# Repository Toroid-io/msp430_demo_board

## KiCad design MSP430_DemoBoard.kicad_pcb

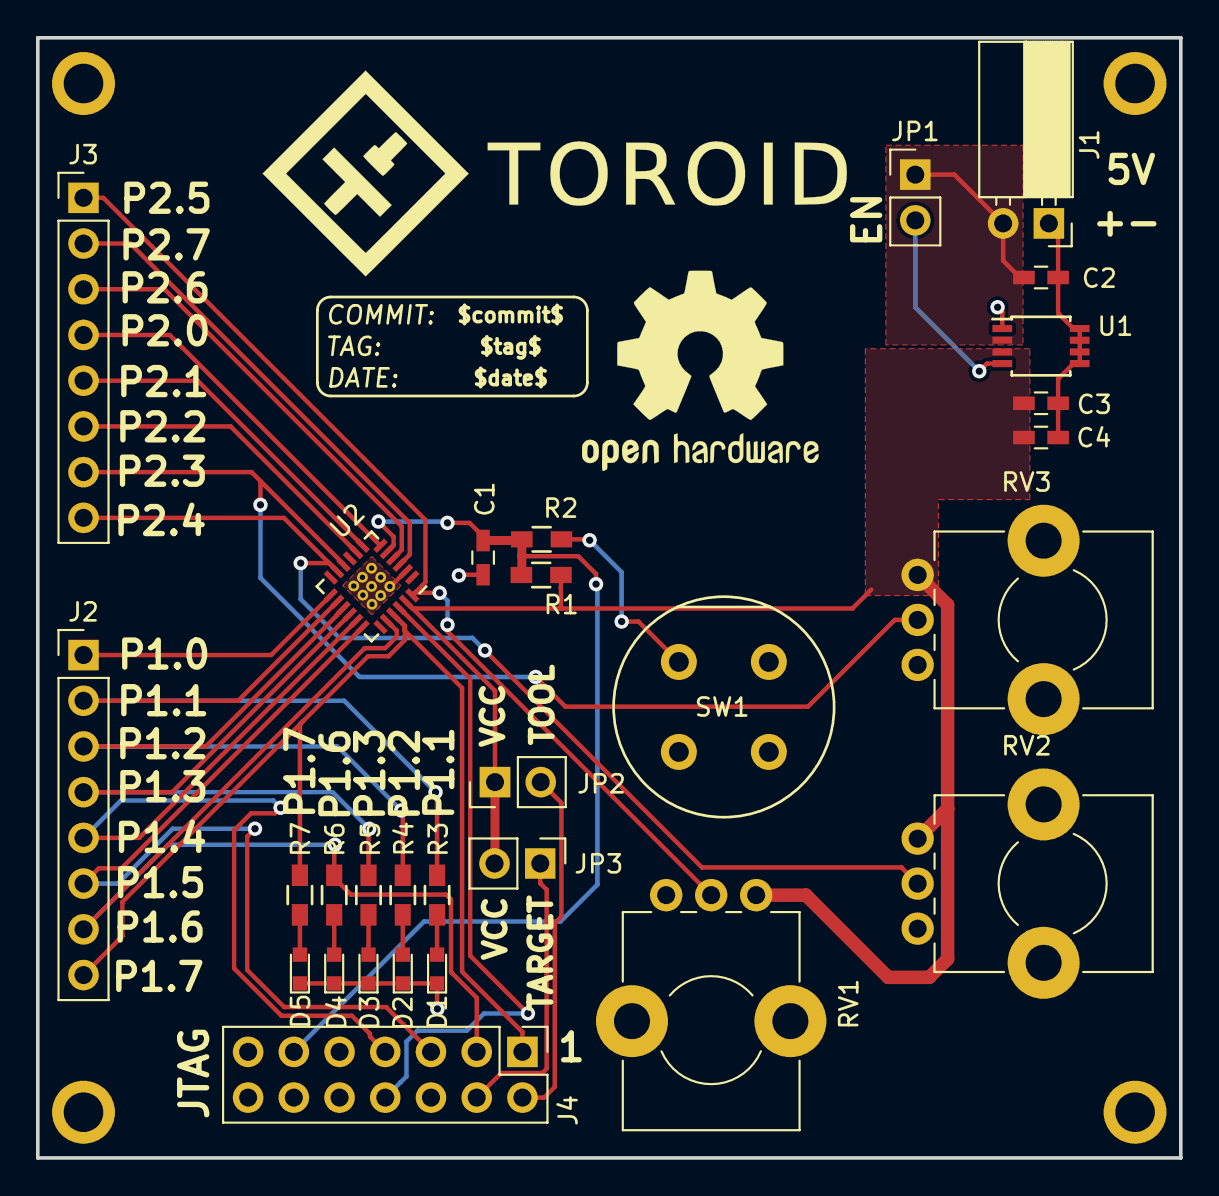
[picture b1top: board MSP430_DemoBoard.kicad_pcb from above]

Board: 2 copper layers, 63.5 x 62.2 mm, 33 parts (0 on the bottom side), 30 nets.

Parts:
C1: 1nF; C_0603_HandSoldering
C2, C3: 100nF; C_0603_HandSoldering
C4: 10uF; C_0603_HandSoldering
D1, D2, D3, D4, D5: LED; LED_0603
J1: VIN; Socket_Strip_Angled_1x02_Pitch2.54mm
J2: P1.X; Pin_Header_Straight_1x08_Pitch2.54mm
J3: P2.X; Pin_Header_Straight_1x08_Pitch2.54mm
J4: JTAG-MSP430; Pin_Header_Straight_2x07_Pitch2.54mm
JP1: Enable; Pin_Header_Straight_1x02_Pitch2.54mm
JP2: VCCTOOL; Pin_Header_Straight_1x02_Pitch2.54mm
JP3: VCCTARGET; Pin_Header_Straight_1x02_Pitch2.54mm
MNT1, MNT2, MNT3, MNT4: MountHole; MountingHole_2.2mm_M2_ISO7380_Pad
R1: 33k; R_0603_HandSoldering
R2, R3, R4, R5, R6, R7: 330; R_0603_HandSoldering
RV1, RV2, RV3: POT; Potentiometer_Bourns_PTV09A-1_Horizontal
SW1: SW_Push_Dual; Push_E-Switch_KS01Q01
U1: ADP1720ARMZ-3.3-R7; TSSOP-8_3x3mm_Pitch0.65mm
U2: MSP430F2101IRGE; QFN-24_4x4mm_Pitch0.5mm_NoMask

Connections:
/P1.0: J2.1, U2.13
/P1.1: J2.2, R3.1, U2.14
/P1.2: J2.3, R4.1, U2.15
/P1.3: J2.4, R5.1, U2.16
/P1.4: J2.5, J4.7, U2.17
/P1.5: J2.6, J4.5, U2.18
/P1.6: J2.7, J4.3, R6.1, U2.20
/P1.7: J2.8, J4.1, R7.1, U2.21
/P2.0: J3.4, U2.6
/P2.1: J3.5, U2.7
/P2.2: J3.6, U2.8
/P2.3: J3.7, RV3.2, U2.10
/P2.4: J3.8, RV2.2, U2.11
/P2.5: J3.1, RV1.2, U2.24
/P2.6: J3.3, U2.4
/P2.7: J3.2, U2.3
/RST: C1.1, J4.11, R1.2, R2.1, U2.5
/TEST: J4.8, U2.22
/VCC: C3.1, C4.1, JP2.1, JP3.2, R1.1, RV1.3, RV2.3, RV3.3, U1.3, U2.23
GND: C1.2, C2.2, C3.2, C4.2, D1.1, D2.1, D3.1, D4.1, D5.1, J1.1, J4.9, RV1.1, RV2.1, RV3.1, SW1.3, U1.1, U1.5, U1.6, U1.7, U1.8, U2.2
unnamed: C2.1, J1.2, JP1.1, U1.2
unnamed: D1.2, R3.2
unnamed: D2.2, R4.2
unnamed: D3.2, R5.2
unnamed: D4.2, R6.2
unnamed: D5.2, R7.2
unnamed: J4.2, JP2.2
unnamed: J4.4, JP3.1
unnamed: JP1.2, U1.4
unnamed: R2.2, SW1.4

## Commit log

2017-03-30 MSP Demo Board, missing route
2017-03-30 Add Toroid and OSH logos
2017-03-31 Routing
2017-03-31 SilkS comments
2017-03-31 Plot options
2017-05-05 Add KiCad CI
2017-05-07 Fix CI
2017-05-07 Fix libraries path
2017-05-07 Update deploy step
2017-05-08 Add Scott branch
2017-05-20 Add step output
2017-05-30 Add commit-trace. Remove signature
2017-05-30 Test
2017-09-07 PCB Update
